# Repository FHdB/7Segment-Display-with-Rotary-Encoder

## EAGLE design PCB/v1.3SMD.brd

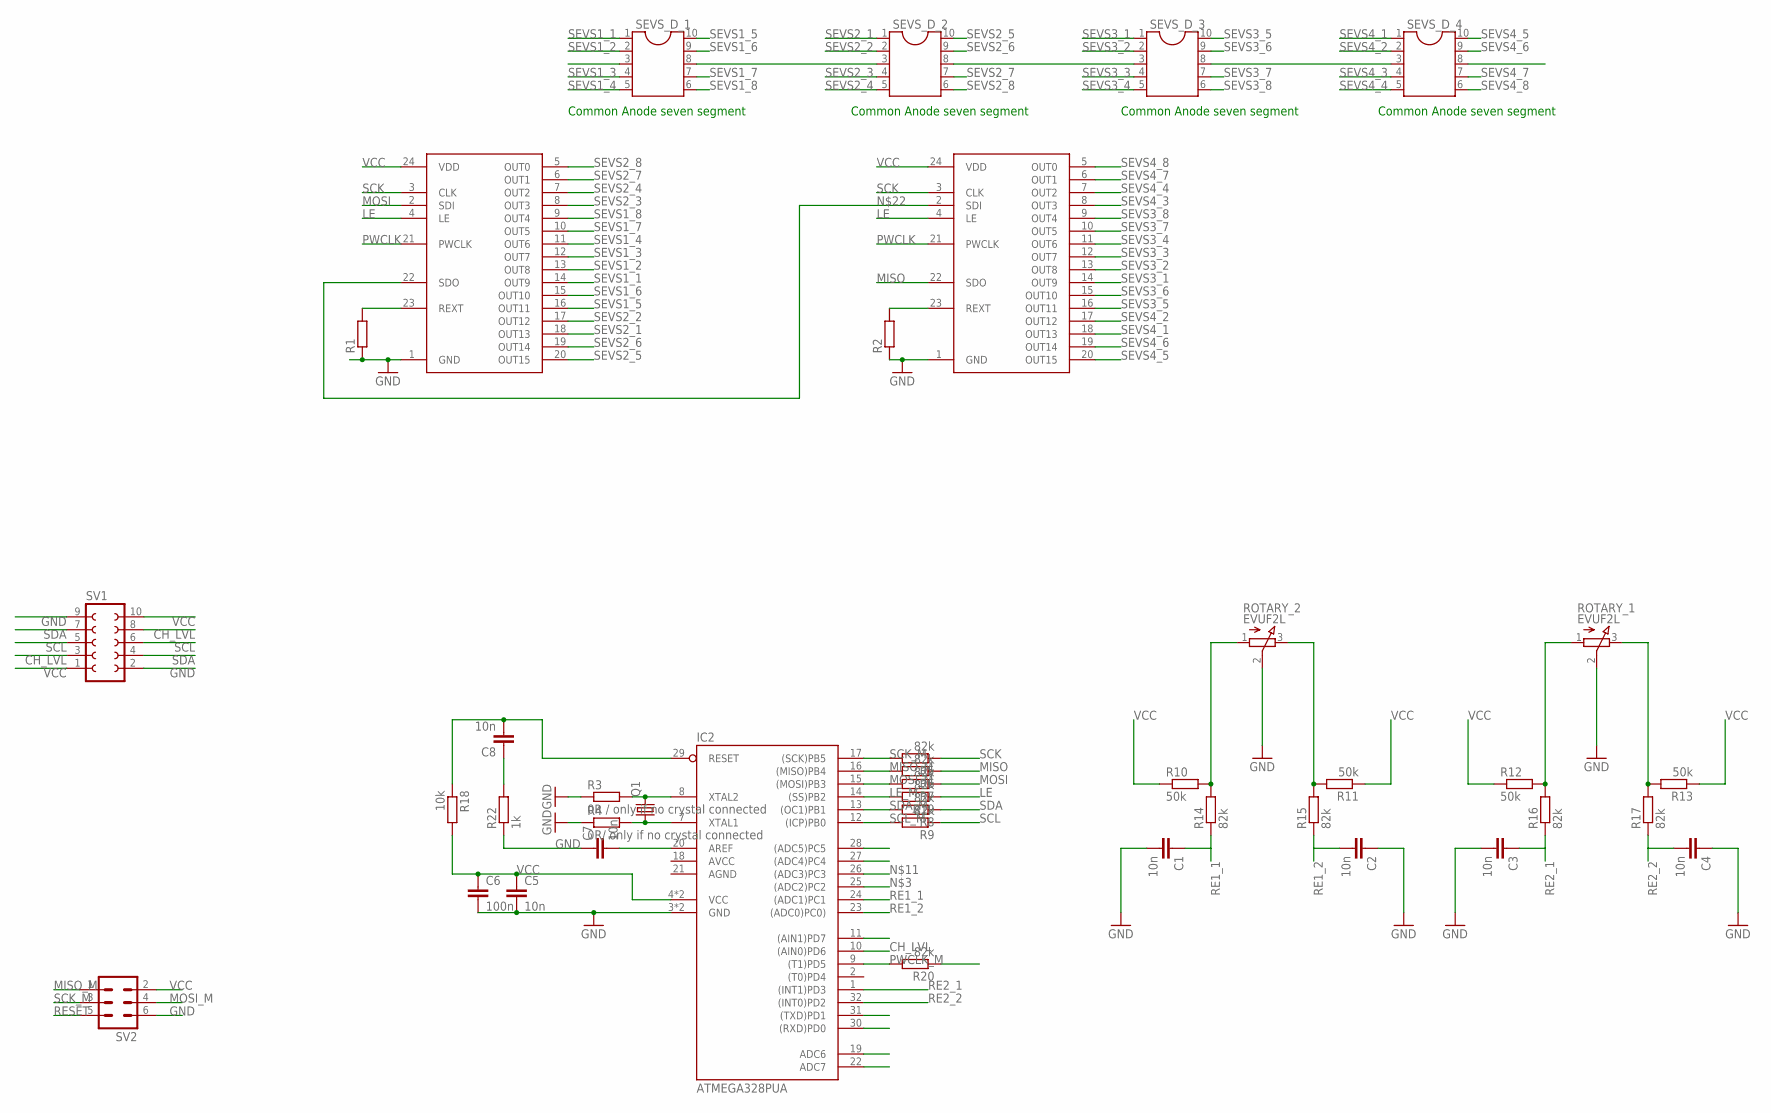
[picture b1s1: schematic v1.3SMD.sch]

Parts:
C1, C2, C3, C4, C5, C7, C8: 10n; C0603
C6: 100n; C0603
IC2: ATMEGA328PUA; TQFP32-08
Q1: CRYSTALSM49; SM49
R1, R2: R-EU_R0603; R0603
R3: 0R / only if no crystal connected; R0603
R4: 0R/ only if no crystal connected; R0603
R5, R6, R7, R8, R9, R14, R15, R16, R17, R19, R20: 82k; R0603
R10, R11, R12, R13: 50k; R0603
R18: 10k; R0603
R22: 1k; R0603
ROTARY_1, ROTARY_2: EVUF2L; EVUFXL
SEVS_D_1, SEVS_D_2, SEVS_D_3, SEVS_D_4: DIL10
SV1: FE05-2
SV2: ML6
U$1, U$2: SPILEDDRIVER; TSSOP24

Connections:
AGND: IC2.21 (AGND)
AVCC: IC2.18 (AVCC)
CH_LVL: IC2.10 ((AIN0)PD6), SV1.3, SV1.8
GND: C1.2, C2.1, C3.2, C4.1, C5.2, C6.2, C7.1, IC2.3 (GND), IC2.5 (GND), R1.1, R2.1, R3.1, R4.1, R22.1, ROTARY_1.2 (S), ROTARY_2.2 (S), SV1.2, SV1.9, SV2.6, U$1.1 (GND), U$2.1 (GND)
LE: R19.1, U$1.4 (LE), U$2.4 (LE)
LE_M: IC2.14 ((SS)PB2), R19.2
MISO: R6.1, U$2.22 (SDO)
MISO_M: IC2.16 ((MISO)PB4), R6.2, SV2.1
MOSI: R7.1, U$1.2 (SDI)
MOSI_M: IC2.15 ((MOSI)PB3), R7.2, SV2.4
unnamed: R11.2, R15.2, ROTARY_2.3 (E)
unnamed: C8.1, R22.2
unnamed: R10.2, R14.2, ROTARY_2.1 (A)
unnamed: R12.2, R16.2, ROTARY_1.1 (A)
unnamed: R13.2, R17.2, ROTARY_1.3 (E)
unnamed: IC2.7 (XTAL1), Q1.1, R4.2
unnamed: IC2.8 (XTAL2), Q1.2, R3.2
unnamed: C7.2, IC2.20 (AREF)
unnamed: U$1.22 (SDO), U$2.2 (SDI)
unnamed: R1.2, U$1.23 (REXT)
unnamed: R2.2, U$2.23 (REXT)
PWCLK: R20.1, U$1.21 (PWCLK), U$2.21 (PWCLK)
PWCLK_M: IC2.9 ((T1)PD5), R20.2
RE1_1: C1.1, IC2.24 ((ADC1)PC1), R14.1
RE1_2: C2.2, IC2.23 ((ADC0)PC0)), R15.1
RE2_1: C3.1, IC2.1 ((INT1)PD3), R16.1
RE2_2: C4.2, IC2.32 ((INT0)PD2), R17.1
RESET: C8.2, IC2.29 (RESET), R18.1, SV2.5
SCK: R5.1, U$1.3 (CLK), U$2.3 (CLK)
SCK_M: IC2.17 ((SCK)PB5), R5.2, SV2.3
SCL: R9.1, SV1.5, SV1.6
SCL_M: IC2.12 ((ICP)PB0), R9.2
SDA: R8.1, SV1.4, SV1.7
SDA_M: IC2.13 ((OC1)PB1), R8.2
SEVS1_1: SEVS_D_1.1, U$1.14 (OUT9)
SEVS1_2: SEVS_D_1.2, U$1.13 (OUT8)
SEVS1_3: SEVS_D_1.4, U$1.12 (OUT7)
SEVS1_4: SEVS_D_1.5, U$1.11 (OUT6)
SEVS1_5: SEVS_D_1.10, U$1.16 (OUT11)
SEVS1_6: SEVS_D_1.9, U$1.15 (OUT10)
SEVS1_7: SEVS_D_1.7, U$1.10 (OUT5)
SEVS1_8: SEVS_D_1.6, U$1.9 (OUT4)
SEVS2_1: SEVS_D_2.1, U$1.18 (OUT13)
SEVS2_2: SEVS_D_2.2, U$1.17 (OUT12)
SEVS2_3: SEVS_D_2.4, U$1.8 (OUT3)
SEVS2_4: SEVS_D_2.5, U$1.7 (OUT2)
SEVS2_5: SEVS_D_2.10, U$1.20 (OUT15)
SEVS2_6: SEVS_D_2.9, U$1.19 (OUT14)
SEVS2_7: SEVS_D_2.7, U$1.6 (OUT1)
SEVS2_8: SEVS_D_2.6, U$1.5 (OUT0)
SEVS3_1: SEVS_D_3.1, U$2.14 (OUT9)
SEVS3_2: SEVS_D_3.2, U$2.13 (OUT8)
SEVS3_3: SEVS_D_3.4, U$2.12 (OUT7)
SEVS3_4: SEVS_D_3.5, U$2.11 (OUT6)
SEVS3_5: SEVS_D_3.10, U$2.16 (OUT11)
SEVS3_6: SEVS_D_3.9, U$2.15 (OUT10)
SEVS3_7: SEVS_D_3.7, U$2.10 (OUT5)
SEVS3_8: SEVS_D_3.6, U$2.9 (OUT4)
SEVS4_1: SEVS_D_4.1, U$2.18 (OUT13)
SEVS4_2: SEVS_D_4.2, U$2.17 (OUT12)
SEVS4_3: SEVS_D_4.4, U$2.8 (OUT3)
SEVS4_4: SEVS_D_4.5, U$2.7 (OUT2)
SEVS4_5: SEVS_D_4.10, U$2.20 (OUT15)
SEVS4_6: SEVS_D_4.9, U$2.19 (OUT14)
SEVS4_7: SEVS_D_4.7, U$2.6 (OUT1)
SEVS4_8: SEVS_D_4.6, U$2.5 (OUT0)
VCC: C5.1, C6.1, IC2.4 (VCC), IC2.6 (VCC), R10.1, R11.1, R12.1, R13.1, R18.2, SEVS_D_1.3, SEVS_D_1.8, SEVS_D_2.3, SEVS_D_2.8, SEVS_D_3.3, SEVS_D_3.8, SEVS_D_4.3, SEVS_D_4.8, SV1.1, SV1.10, SV2.2, U$1.24 (VDD), U$2.24 (VDD)

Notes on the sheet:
Common Anode seven segment

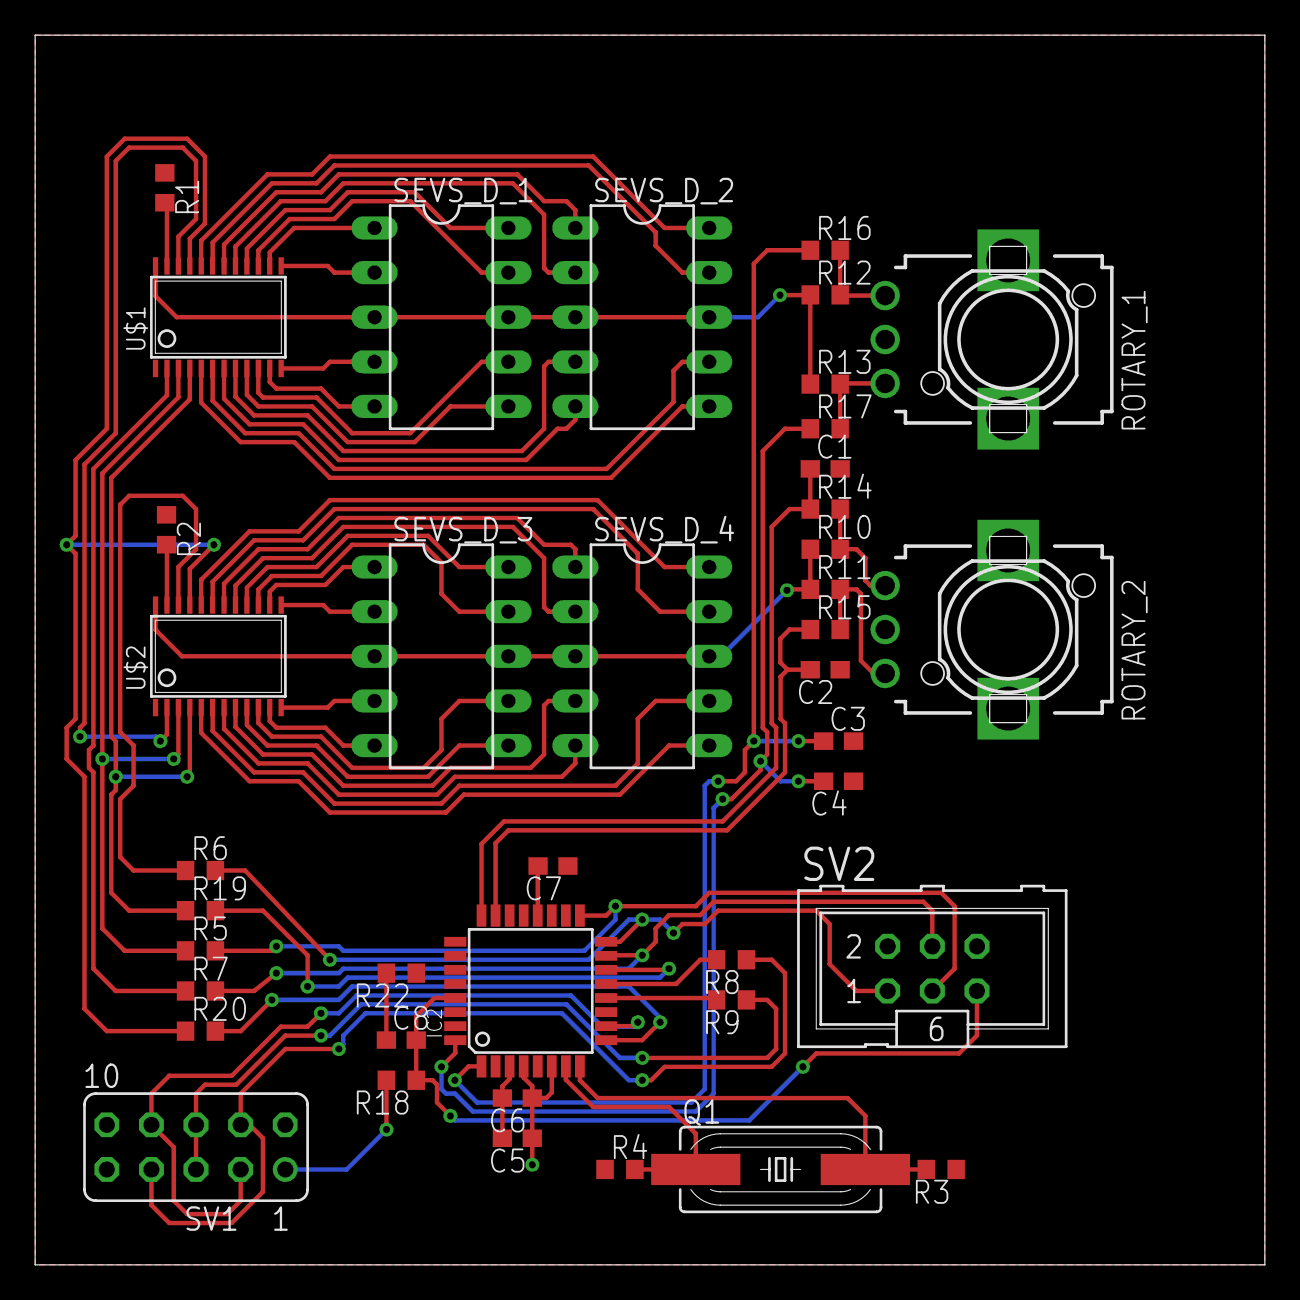
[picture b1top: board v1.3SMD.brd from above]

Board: 2 copper layers, 70.0 x 70.0 mm, 41 parts (0 on the bottom side), 65 nets.

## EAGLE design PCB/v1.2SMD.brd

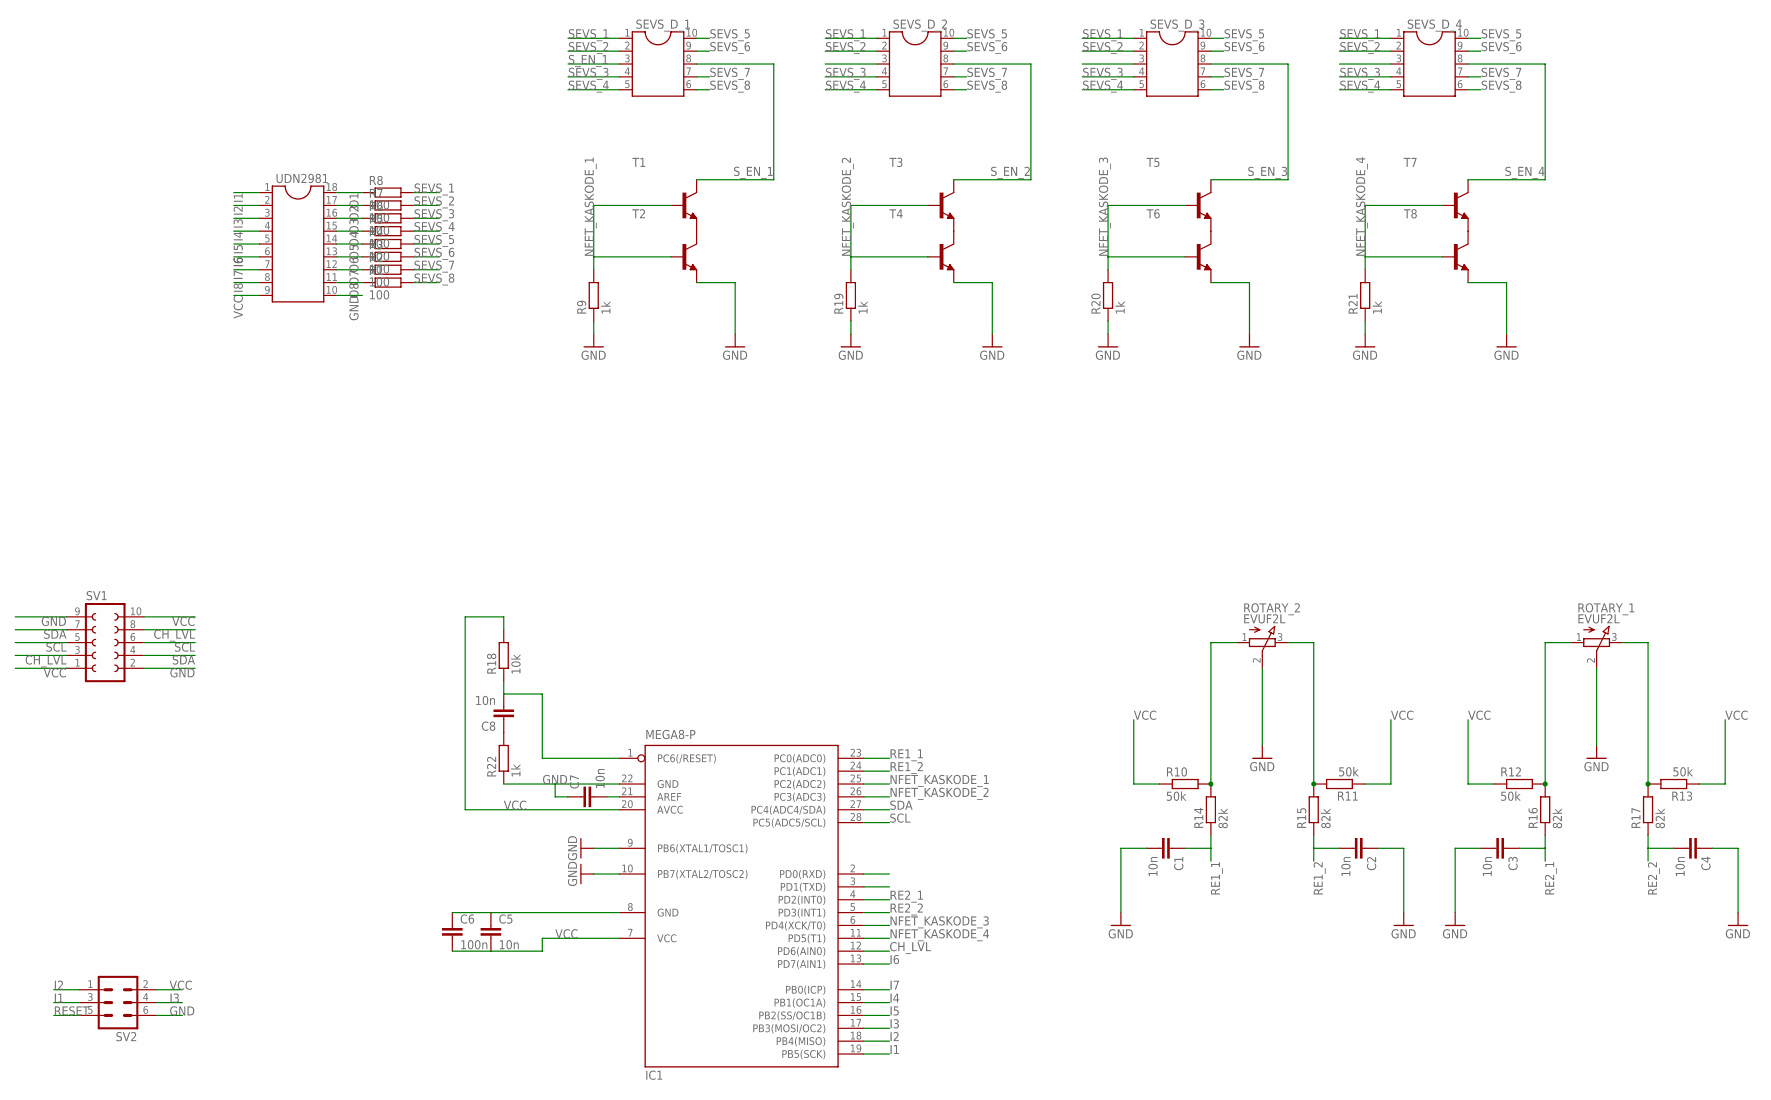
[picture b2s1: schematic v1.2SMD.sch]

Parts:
C1, C2, C3, C4, C5, C7, C8: 10n; C0603
C6: 100n; C0603
IC1: MEGA8-P; DIL28-3
R1, R2, R3, R4, R5, R6, R7, R8: 100; R0603
R9, R19, R20, R21, R22: 1k; R0603
R10, R11, R12, R13: 50k; R0603
R14, R15, R16, R17: 82k; R0603
R18: 10k; R0603
ROTARY_1, ROTARY_2: EVUF2L; EVUFXL
SEVS_D_1, SEVS_D_2, SEVS_D_3, SEVS_D_4: DIL10
SV1: FE05-2
SV2: ML6
T1, T2, T3, T4, T5, T6, T7, T8: BC808-NPN-SOT23-BEC; SOT23-BEC
UDN2981: DIL18

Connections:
CH_LVL: IC1.12 (PD6(AIN0)), SV1.3, SV1.8
GND: C1.2, C2.1, C3.2, C4.1, C7.1, IC1.9 (PB6(XTAL1/TOSC1)), IC1.10 (PB7(XTAL2/TOSC2)), IC1.22 (GND), R9.1, R19.1, R20.1, R21.1, R22.1, ROTARY_1.2 (S), ROTARY_2.2 (S), SV1.2, SV1.9, SV2.6, T2.E, T4.E, T6.E, T8.E, UDN2981.10
I1: IC1.19 (PB5(SCK)), SV2.3, UDN2981.1
I2: IC1.18 (PB4(MISO)), SV2.1, UDN2981.2
I3: IC1.17 (PB3(MOSI/OC2)), SV2.4, UDN2981.3
I4: IC1.15 (PB1(OC1A)), UDN2981.4
I5: IC1.16 (PB2(SS/OC1B)), UDN2981.5
I6: IC1.13 (PD7(AIN1)), UDN2981.6
I7: IC1.14 (PB0(ICP)), UDN2981.7
I8: UDN2981.8
unnamed: R11.2, R15.2, ROTARY_2.3 (E)
unnamed: C8.1, R22.2
unnamed: R10.2, R14.2, ROTARY_2.1 (A)
unnamed: R12.2, R16.2, ROTARY_1.1 (A)
unnamed: R13.2, R17.2, ROTARY_1.3 (E)
unnamed: T1.E, T2.C
unnamed: T3.E, T4.C
unnamed: T5.E, T6.C
unnamed: T7.E, T8.C
unnamed: C5.1, C6.1, IC1.8 (GND)
unnamed: C7.2, IC1.21 (AREF)
NFET_KASKODE_1: IC1.25 (PC2(ADC2)), R9.2, T1.B, T2.B
NFET_KASKODE_2: IC1.26 (PC3(ADC3)), R19.2, T3.B, T4.B
NFET_KASKODE_3: IC1.6 (PD4(XCK/T0)), R20.2, T5.B, T6.B
NFET_KASKODE_4: IC1.11 (PD5(T1)), R21.2, T7.B, T8.B
O1: R8.1, UDN2981.18
O2: R7.1, UDN2981.17
O3: R6.1, UDN2981.16
O4: R5.1, UDN2981.15
O5: R4.1, UDN2981.14
O6: R3.1, UDN2981.13
O7: R2.1, UDN2981.12
O8: R1.1, UDN2981.11
RE1_1: C1.1, IC1.23 (PC0(ADC0)), R14.1
RE1_2: C2.2, IC1.24 (PC1(ADC1)), R15.1
RE2_1: C3.1, IC1.4 (PD2(INT0)), R16.1
RE2_2: C4.2, IC1.5 (PD3(INT1)), R17.1
RESET: C8.2, IC1.1 (PC6(/RESET)), R18.1, SV2.5
SCL: IC1.28 (PC5(ADC5/SCL)), SV1.5, SV1.6
SDA: IC1.27 (PC4(ADC4/SDA)), SV1.4, SV1.7
SEVS_1: R8.2, SEVS_D_1.1, SEVS_D_2.1, SEVS_D_3.1, SEVS_D_4.1
SEVS_2: R7.2, SEVS_D_1.2, SEVS_D_2.2, SEVS_D_3.2, SEVS_D_4.2
SEVS_3: R6.2, SEVS_D_1.4, SEVS_D_2.4, SEVS_D_3.4, SEVS_D_4.4
SEVS_4: R5.2, SEVS_D_1.5, SEVS_D_2.5, SEVS_D_3.5, SEVS_D_4.5
SEVS_5: R4.2, SEVS_D_1.10, SEVS_D_2.10, SEVS_D_3.10, SEVS_D_4.10
SEVS_6: R3.2, SEVS_D_1.9, SEVS_D_2.9, SEVS_D_3.9, SEVS_D_4.9
SEVS_7: R2.2, SEVS_D_1.7, SEVS_D_2.7, SEVS_D_3.7, SEVS_D_4.7
SEVS_8: R1.2, SEVS_D_1.6, SEVS_D_2.6, SEVS_D_3.6, SEVS_D_4.6
S_EN_1: SEVS_D_1.3, SEVS_D_1.8, T1.C
S_EN_2: SEVS_D_2.3, SEVS_D_2.8, T3.C
S_EN_3: SEVS_D_3.3, SEVS_D_3.8, T5.C
S_EN_4: SEVS_D_4.3, SEVS_D_4.8, T7.C
VCC: C5.2, C6.2, IC1.7 (VCC), IC1.20 (AVCC), R10.1, R11.1, R12.1, R13.1, R18.2, SV1.1, SV1.10, SV2.2, UDN2981.9

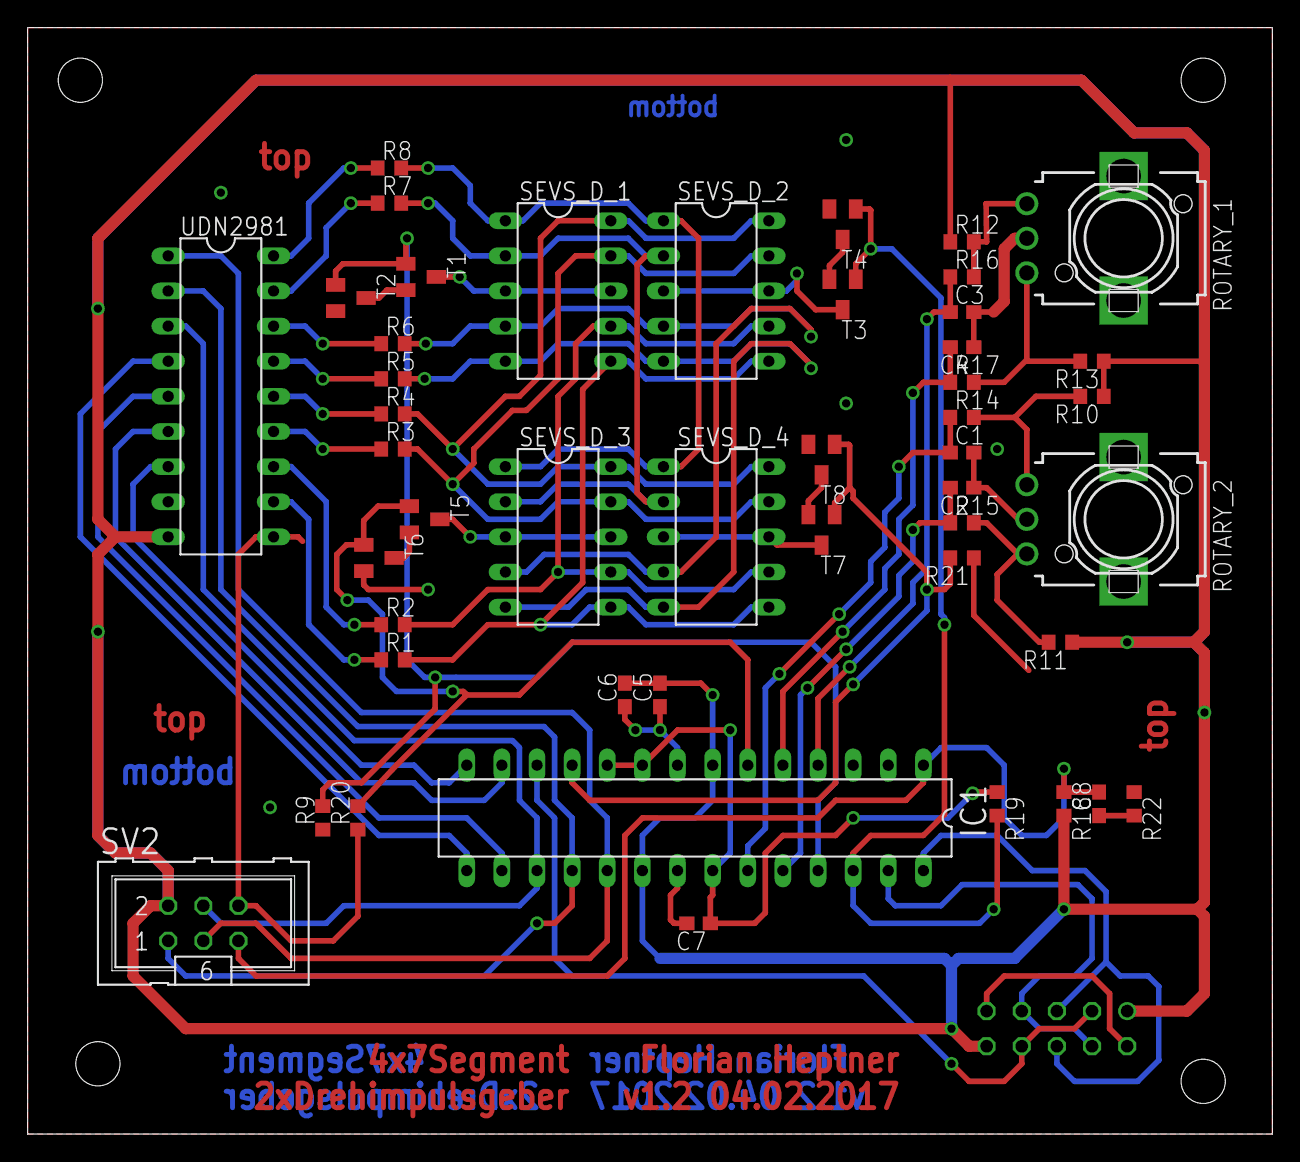
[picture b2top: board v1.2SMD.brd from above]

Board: 2 copper layers, 90.0 x 80.0 mm, 48 parts (1 on the bottom side), 52 nets.

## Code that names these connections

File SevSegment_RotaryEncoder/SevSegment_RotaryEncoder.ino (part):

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/*
7Segment Test:

13: PB5
12: PB4
11: PB3
10: PB2
09: PB1
08: PB0
07: PD7

V1.0 - !!OBSOLETE!! Wiring changed

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uint8_t sev_seg_3 = 11;
uint8_t sev_seg_4 = 11;

#define ch_lvl_pin  6

/*
  Rotary Encoder constants and variables
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  pinMode(13,OUTPUT);
  
  //
  pinMode(ch_lvl_pin,OUTPUT);
  digitalWrite(ch_lvl_pin,LOW);
  
  sev_seg_counter = 0;
  
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      if(dimValue>0)
      {
        dimValue = dimValue - 1;
        digitalWrite(ch_lvl_pin, HIGH);
      }
    }    
    else
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      if(dimValue<100)
      {
        dimValue = dimValue + 1;
        digitalWrite(ch_lvl_pin, HIGH);
      }
    }
    sev_seg_3 = dimValue/10;
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      if(address>0)
      {
        address = address - 1;
        digitalWrite(ch_lvl_pin, HIGH);    
      }
    }    
    else
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      if(address<64)
      {
        address = address + 1;
        digitalWrite(ch_lvl_pin, HIGH);    
      }
    }
    sev_seg_1 = address/10;
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  array[1] = address;
  array[4] = dimValue;
  Wire.write(array,6); // respond with message of 6 bytes
  digitalWrite(ch_lvl_pin, LOW);
  // as expected by master
}

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
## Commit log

2016-02-07 7Segment Display And Rotary Encoder Through Hole PCB
2016-02-09 Seven Segment, Rotary Encoder, I2C
    This example code is written for a 4-PCB setup. The 4 displays/rotary
    encoders are used as user interface for an i2c connected master that
    controls lamps. The first number is a 6-bit-address, the second number
    is a dim value for values from 0 to 100 ("A0" due to the limitation of
    only having two digits).
2016-12-05 Codemercs warrior DALI boards
    Added Codemercs Warrior Board library with Warrior09 Mod 1 (Master) and
    Warrior11 (Bus supply)
2016-12-05 moved to different project
2017-01-29 Tidying up
    Some useful order in schematic
2017-02-04 Rerouting and resizing
    Smaller packages and some optimizations
2017-02-05 Replaced NMos package
    replaced CBE with much more common BEC package
2017-02-05 routing
    optimized some routes
2017-02-08 diameter correction
    corrected diameter for rotary encoder
2017-02-08 New version with LED drivers
    started a new version with generic 16channel LED driver in TSSOP24 and
    Atmega328PU in TQFP32 package. These parts potentially allow for smaller
    outer dimensions
2017-02-09 added resistors
    added resistors to data lines for current limitation. You could also add
    capacitors in order to have a low pass filter but I rely on the gat
    input capacity of the ICs instead.
2017-02-14 Finished routing
    connected all air wires and finished placing. Still need to finish up
    labels and positions in silk screen

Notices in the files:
SevSegment_RotaryEncoder/SevSegment_RotaryEncoder.ino:
This program is free software: you can redistribute it and/or modify
it under the terms of the GNU General Public License as published by
the Free Software Foundation, either version 3 of the License, or
(at your option) any later version.
der GNU General Public License, wie von der Free Software Foundation,
Version 3 der Lizenz oder (nach Ihrer Wahl) jeder neueren
Siehe die GNU General Public License für weitere Details.
Sie sollten eine Kopie der GNU General Public License zusammen mit diesem
